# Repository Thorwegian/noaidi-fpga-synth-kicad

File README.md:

# Noaidi FPGA Synth: the board

The KiCad project for the Noaidi synthesizer's circuit board, in
progress. The gateware and firmware that run on it live in
[Thorwegian/noaidi-fpga-synth](https://github.com/Thorwegian/noaidi-fpga-synth),
and the synth itself is presented at [thj.no/synth](https://thj.no/synth/).

## What is on it

The board is a carrier for three off-the-shelf modules and the few parts
around them, numbered as in the picture:

1. **Two DIN MIDI inputs** (J1, J2) through H11L1 optocouplers (U3, U4),
   the six-legged part below each socket: one for the keyboard, one for
   the dev host.
2. **ESP32-S3-DevKitC** (U1) on headers: MIDI, voices, presets and the
   console. The picture shows Espressif's board; the boards in hand are
   copies with the same pin layout (`docs/yd_esp32_s3.md`).
3. **Tang Nano 20K** (U2) on headers: the sound engine.
4. **Adafruit PCM510x I2S DAC module** (U5): analog audio out, on its
   own 3.5 mm jack and on a pin header.
5. **RCA socket** (J3): S/PDIF out.
6. **USB-C socket for power** (J9), into each module's 5 V rail through
   an LM66100 ideal diode (U6, U7).
7. **USB-C socket for data** (J14): the ESP32's USB data pair, below the
   module's USB pins.
8. **Pin headers** for the second SPI bus, two I2C buses, UART0, I2S and
   S/PDIF, the ESP32 module's 5 V beside the UART for a front panel
   board, and 29 test points.
9. **Four RGBW LEDs** (D3–D6) in a chain, on the ESP32's GPIO21 through a
   buffer (U8), for a light inside the case.

Two layers, 78.43 × 160.58 mm by `kicad-cli pcb export stats`, both
filled with ground. The modules, the DIN and RCA sockets, the pin
headers and the test points are through-hole; the other parts are
surface-mount.

The board is made from the circuit in text by script: see The circuit
in text, below.

## Layout

Front copper and silkscreen:

Back copper, mirrored:

The three modules are rendered from 3D models of them, each standing in
a socket of two rows of female pin headers: the Tang Nano 20K from
Sipeed's model (`docs/thirdparty/Tang_Nano_20K_3921.step`), the ESP32
module from the model of the ESP32-S3-DevKitC-1-N8R2
(`docs/thirdparty/ESP32-S3-DEVKITC-1-N8R2.STEP`), the DAC module from
Adafruit's model (`docs/thirdparty/6250 PCM510x I2S DAC.step`). The
first two models have the module's pin headers; Adafruit's has none,
and KiCad's model of a pin header stands in under each of its rows.
Each module's underside is 11.04 mm above the base board: the 8.5 mm of
the socket, from KiCad's model of it, and the 2.54 mm body of the
module's pin headers.

The DIN sockets are rendered from a model made of Lumberg's two
(`docs/thirdparty/lumberg_0105_05_with_pins_of_08-1.step`): the body is
that of Lumberg's model of the 0105 05, with its contacts cut off at
the body's underside, and the solder pins below it are those of poles
1 to 5 and the two ground pins of Lumberg's model of the 8-pole
version, the 0105 08-1. Those pins are where Lumberg's drawing and the
footprint have them, which the 0105 05 model's own are not. The colours
are the project's: dark grey for the plastic, as the part is, and
tinned metal for the contacts and pins.

The RCA socket is rendered from Kycon's model of the part
(`docs/thirdparty/KLPX-0848A-2-x.IGS`), unaltered: the housing is dark,
as that of the black KLPX-0848A-2-B is, and the barrel reaches beyond
the board's bottom edge.

The two USB sockets are rendered from a model of the Hroparts
TYPE-C-31-M-12 that is not its maker's
(`docs/thirdparty/Hroparts_TYPE-C-31-M-12_model_ai03.step`). It is a
simplified one: a single solid in one colour, with twelve solder tails
where the part has sixteen, the two of each supply and ground pair
drawn as one. Its shell, mouth, legs and pegs are where Hroparts'
drawing has them.

The four LEDs are rendered from the model in JLCPCB's library for
OPSCO's SKC6812RGBW-WS, C5378724
(`docs/thirdparty/SKC6812RGBW_model_EasyEDA.step`): 5.1 × 4.9 × 1.6 mm
over its leads, where OPSCO's data sheet has 5.0 × 4.85 × 1.6, with the
cut corner of its top at pad 1.

The ESP32 module's model is from DigiKey's page for the part, the DAC
module's from Adafruit's repository of CAD files on GitHub
([adafruit/Adafruit_CAD_Parts](https://github.com/adafruit/Adafruit_CAD_Parts)).
Of Lumberg's two DIN socket models, the 0105 05's is from DigiKey's
page for the part and the 0105 08-1's from
[Lumberg's page for the 0105](https://www.lumberg.com/en/products/product/0105),
which carries the same file of the 0105 05 as DigiKey. The RCA socket's
model is Kycon's own, and so is its
[dimension drawing](https://cloud.kycon.com/Pub_Eng_Draw/KLPX-0848A-2-x.pdf).
The USB sockets' model is ai03's, from the KiCad library
[ai03-2725/Type-C.pretty](https://github.com/ai03-2725/Type-C.pretty)
on GitHub, which states no licence. The LEDs' model is the one
EasyEDA's library holds for the package
`LED-SMD_4P-4.9-W4.9-LS5.0-BR`, fetched from EasyEDA by
the uuid in `docs/thirdparty/jlcpcb-library/C5378724.json`; it states
no licence either.

## Files

The root folder holds the KiCad project, this README, `AGENTS.md` and
the licence. Scripts go in `scripts/`, documents in `docs/`.

- `AGENTS.md`: the rules for AI agents working in this repository, who
  does what, and where to start reading.
- `noaidi-fpga-synth.kicad_pro`, `.kicad_pcb`, `.kicad_dru`: the KiCad
  project, which holds the board and its design rules. It has no
  schematic: the circuit is in `circuit/`.
- `noaidi-fpga-synth.kicad_sym` and `noaidi-fpga-synth.pretty/`: the
  project's own symbols and footprints (the two modules, the DAC, the
  DIN sockets, the RCA and USB-C connectors). The ESP32 module's
  footprint is Espressif's, from
  [espressif/kicad-libraries](https://github.com/espressif/kicad-libraries)
  (CC-BY-SA 4.0 with the exception KiCad's own libraries have), with a
  keep-out for copper fills under the antenna and, beside each pad of
  pins 23 to 44, a second hole 2.54 mm further out on the same copper:
  Espressif's board has its pin rows 22.86 mm apart, the HW-678 has
  them 25.4 mm apart, and either plugs in. The USB sockets'
  footprint, `USB_C_Receptacle_HRO_TYPE-C-31-M-12`, is the one of that
  name in KiCad's library `Connector_USB` (the same licence), naming a
  3D model that the repository holds: KiCad's names one that KiCad does
  not ship.
- `scripts/render.sh`: makes the board's images on this page, into
  `build/` (the page shows the copies in `docs/images/`), with
  `kicad-cli` (KiCad 10), and with them the view at an angle from the
  other side, the sockets at the board's top edge facing the camera
  (`build/pcb-iso-rear.jpg`); `scripts/crop.py` trims each 3D render to
  the board and the parts on it, what reaches beyond the board's edge
  included, and `scripts/parts_picture.py` numbers the parts in the view
  from above (`build/pcb-parts.jpg`)
- `scripts/render_enclosure.sh`: renders the board in a clear acrylic
  enclosure, lit in the dark by LEDs inside the acrylic, into
  `build/enclosure-<shot>.png`, one picture for each of its shots, with
  `kicad-cli` and Blender; `scripts/enclosure_scene.py` builds the scene
  around the board's 3D model, with an opening in the wall for each part
  at an edge, lists the shots and says how the light is modelled. The
  picture at the top of this page is its shot `left-bottom-low`. The
  enclosure is the picture's and decides nothing about the one that will
  be built.
- `circuit/`: the circuit described in Python with SKiDL, one file
  per sheet (`usb.py`, `esp32.py`, `tang_nano_20k.py`, `test_points.py`),
  the nets that cross sheets in `global_nets.py`, the parts used on more
  than one sheet in `parts.py`, and `board.py` for the whole board. See
  The circuit in text, below. `designators.toml` lists each part's
  designator by the path of tags that leads to the part
  (`esp32.midi1_input.opto` is U3), and `designators.py` gives every part
  its designator from it: the sheets name none. `board.py` writes a new
  part's line into it, with the next free number, and retires the
  designator of a part that is gone. `esp32_minimal.py` is the ESP32-S3-WROOM-1
  module with the least that belongs to it, after Espressif's
  ESP32-S3-DevKitC-1; no sheet uses it, as the board carries the bought
  module.
- `scripts/layout_pictures.py`: pictures of the board's copper and print to judge
  a layout by: the whole board, its quarters, tiles small enough for an
  agent to see every track, each layer with its fill, and the fills
  laid over each other.
- `scripts/fab_files.py`: writes what JLCPCB's order page takes into
  `build/fab/`: the Gerber and drill files as one archive, the list of
  the parts JLCPCB places, and the list of where each of them sits.
- `scripts/cost_estimate.py`: prints what an order of the board costs at
  JLCPCB, delivered to Norway with VAT: the parts and the assembly fees
  fetched from JLCPCB as it runs, the bare boards and shipping at the
  prices read from JLCPCB's quote page.
- `scripts/netlist_import.py`: what KiCad's File > Import > Netlist
  would list for the netlist `circuit/board.py` writes and the board, in
  the dialog's own wording and without running KiCad, so that a mistake
  in the circuit is found before anyone opens the board. It links
  footprints by their tstamps, the dialog's "Link footprints using
  component tstamps (unique ids)", unless it is given `--by-designator`.
  KiCad's dialog is the authority; this is the check that comes first.
- `docs/pins.md`: which pin of which module carries what, the
  connectors, the test points, and each part's name in the code.
  Written by `circuit/board.py`; not edited by hand.
- `docs/requirements.md`: what the board has to do; the circuit and
  the layout are checked against it.
- [`docs/yd_esp32_s3.md`](docs/yd_esp32_s3.md): the YD-ESP32-S3, the
  design of the ESP32-S3 boards in hand, and those boards in detail.
- `docs/thirdparty/`: the vendors' documents the board is drawn from.
  Mechanical: the Tang Nano 20K's dimension drawing (`.pdf`, `.dxf`) and
  3D model (`.step`), the ESP32-S3-DevKitC-1-N8R2's 3D model (`.STEP`),
  the HW-678's manual from its seller (`.pdf`) and the dimension drawing
  of the YD-ESP32-S3, the design it copies, from its designer (`.pdf`),
  the Adafruit PCM510x's 3D model (`.step`) and fab print with its
  dimensions, a 3D model of the Lumberg 0105 05 DIN socket made
  from Lumberg's models of the 0105 05 and the 0105 08-1 (`.step`),
  Kycon's 3D model of the KLPX-0848A-2-x RCA socket (`.IGS`) with its
  dimension drawing, which has the recommended PCB layout, ai03's
  3D model of the Hroparts TYPE-C-31-M-12 USB-C socket (`.step`) and
  EasyEDA's 3D model of the SKC6812 RGBW LED (`.step`).
  Electrical: the Tang Nano 20K's schematic and pinout, the
  GW2AR data sheet, the ESP32-S3-DevKitC-1 user guide and pinouts, and
  Espressif's reference design for that board (v1.1) in a folder of its
  own: the schematic, the layout as a PADS file, the Gerber files, the
  fabrication requirements, the bill of materials and the placement
  list. The YD-ESP32-S3's schematic (V1.4) from its designer. Then the
  Adafruit PCM510x guide and schematic, the 6N138 MIDI input circuit and
  the TOTX1950A optical transmitter's data sheet. The board's own parts,
  from the links in their symbols' Datasheet fields: the LM66100 ideal
  diode (U6, U7), the H11L1 optocoupler (U3, U4; onsemi's data sheet,
  which the symbol names, and Everlight's, whose part is the one
  chosen), the 1N4148W diode (D1, D2), the Lumberg 0105 DIN socket
  (J1, J2), the Kycon KLPX RCA socket (J3), the Hroparts
  TYPE-C-31-M-12 USB-C socket (J9, J14; drawing) and OPSCO's SKC6812RGBW
  LED (D3–D6). Two parts that are
  not on the board: the 6N138 optocoupler and the GCT USB4085 USB-C
  receptacle (specification and drawing). The parts of
  `circuit/esp32_minimal.py`, which are not on the board either: the
  ESP32-S3-WROOM-1 module and JSCJ's SS8050 transistor.

## Build tools

`kicad-cli` (KiCad 10), `pdftoppm` (poppler-utils), `blender` (4, with
Cycles, for `scripts/render_enclosure.sh`) and
`java` (25, for Freerouting, whose jar `scripts/route.sh` fetches into
`build/tools/`) come from the system's packages, and so does the Python
with KiCad's `pcbnew` module and Pillow (python3-pil) that the scripts
which read the board file run under. The other Python
tools are listed in
`scripts/requirements.txt` and live in a virtual environment, `.venv/`
at the root, which is not committed:

    python3 -m venv .venv
    .venv/bin/pip install -r scripts/requirements.txt
    source .venv/bin/activate

- `skidl`: circuits described in Python. It is not in Ubuntu's packages.
  It finds KiCad's symbol libraries through the environment variable
  `KICAD10_SYMBOL_DIR` (`/usr/share/kicad/symbols` on Ubuntu). It also
  looks for KiCad 5 to 9 on every run, and warns about each one that is
  not installed. `circuit/.skidlcfg` gives those five an empty answer; it
  is read from SKiDL's own folder, where it is put once on each machine
  (`~/Library/Application Support/skidl` on macOS):

      mkdir -p ~/.local/share/skidl
      cp circuit/.skidlcfg ~/.local/share/skidl/
- `pillow`: for `scripts/crop.py` and `scripts/parts_picture.py`.

## The circuit in text

`circuit/` describes the board's circuit in Python, and it is where the
circuit is designed. It holds the parts chosen for fabrication: 0805
resistors and capacitors, H11L1 optocouplers, two surface-mount USB-C
sockets (one for power, one for the ESP32's USB data), no ferrite
bead, and one S/PDIF coaxial output (J3, the 96 kHz stream; the 48 kHz
stream is on its header only).

Copyright © 2026 Thor H. Linløkken <thj@thj.no>
License: [CERN-OHL-S v2](LICENSE.txt)

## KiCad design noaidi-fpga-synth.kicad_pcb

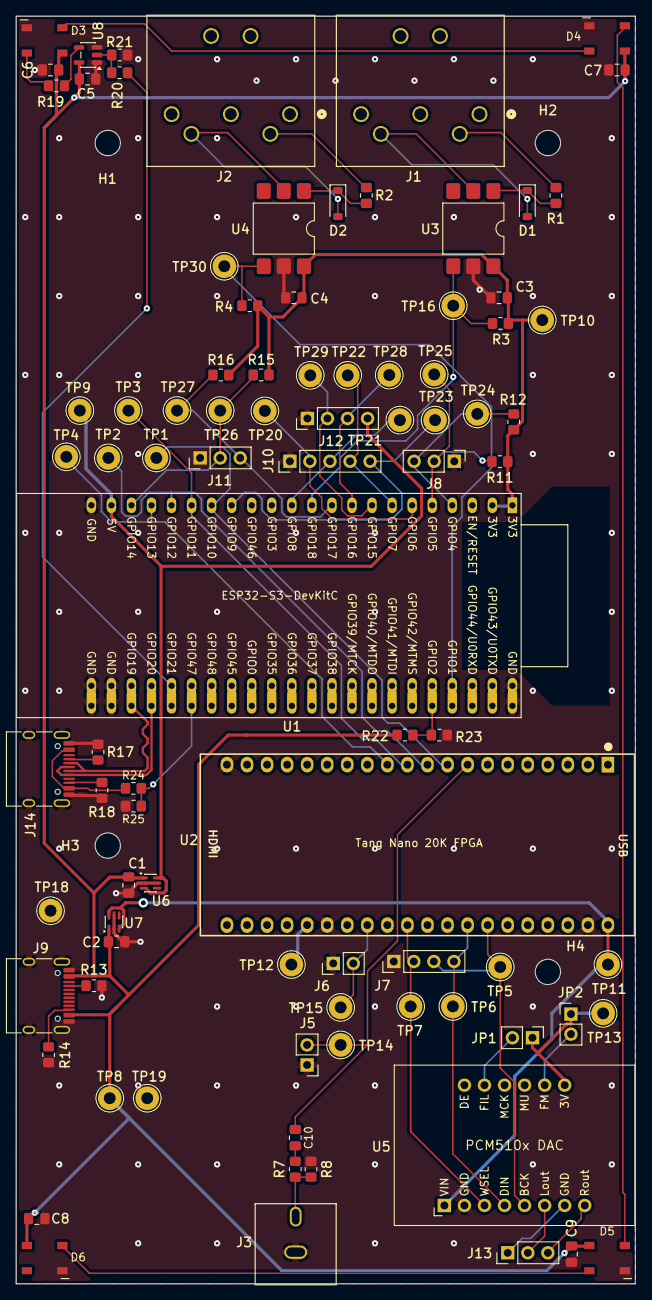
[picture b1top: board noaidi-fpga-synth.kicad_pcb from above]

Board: 2 copper layers, 78.4 x 160.6 mm, 93 parts (0 on the bottom side), 57 nets.

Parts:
C1, C2: 1u; C_0805_2012Metric_Pad1.18x1.45mm_HandSolder
C3, C4, C6, C7, C8, C9, C10: 100n; C_0805_2012Metric_Pad1.18x1.45mm_HandSolder
C5: 10u; C_0805_2012Metric_Pad1.18x1.45mm_HandSolder
D1, D2: 1N4148W; D_SOD-123
D3, D4, D5, D6: LED_SKC6812RGBW; LED_SKC6812RGBW_5.0x4.85mm
H1, H2, H3, H4: MountingHole; MountingHole_3.2mm_M3
J1, J2: Lumberg_0105_05
J3: Conn_Coaxial; RCA_Kycon_KLPX-0848A
J5, J6: Conn_01x02_Pin; PinHeader_1x02_P2.54mm_Vertical
J7, J12: Conn_01x04_Pin; PinHeader_1x04_P2.54mm_Vertical
J8, J11, J13: Conn_01x03_Pin; PinHeader_1x03_P2.54mm_Vertical
J9, J14: USB_C_Receptacle_USB2.0_16P; USB_C_Receptacle_HRO_TYPE-C-31-M-12
J10: Conn_01x05_Pin; PinHeader_1x05_P2.54mm_Vertical
JP1, JP2: Jumper_2_Open; PinHeader_1x02_P2.54mm_Vertical
R1, R2, R7: 220; R_0805_2012Metric_Pad1.20x1.40mm_HandSolder
R3, R4, R19: 470; R_0805_2012Metric_Pad1.20x1.40mm_HandSolder
R8: 120; R_0805_2012Metric_Pad1.20x1.40mm_HandSolder
R11, R12, R15, R16, R23: 4.7k; R_0805_2012Metric_Pad1.20x1.40mm_HandSolder
R13, R14, R17, R18: 5.1k; R_0805_2012Metric_Pad1.20x1.40mm_HandSolder
R20: 1k; R_0805_2012Metric_Pad1.20x1.40mm_HandSolder
R21, R22: 10k; R_0805_2012Metric_Pad1.20x1.40mm_HandSolder
R24: 100k; R_0805_2012Metric_Pad1.20x1.40mm_HandSolder
R25: 150k; R_0805_2012Metric_Pad1.20x1.40mm_HandSolder
TP1, TP2, TP3, TP4, TP5, TP6, TP7, TP8, TP9, TP10, TP11, TP12, TP13, TP14, TP15, TP16, TP18, TP19, TP20, TP21, TP22, TP23, TP24, TP25, TP26, TP27, TP28, TP29, TP30: TestPoint; TestPoint_THTPad_D3.0mm_Drill1.5mm
U1: ESP32-S3-DevKitC
U2: Tang_Nano_20K; DIP-40_TangNano20K
U3, U4: H11L1; SMDIP-6_W9.53mm
U5: Adafruit_PCM510x
U6, U7: LM66100DCK; SOT-363_SC-70-6
U8: 74AHCT1G125; SOT-23-5

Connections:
DAC_FIL: JP1.2, U5.13
DAC_FM: JP2.2, U5.10
DAC_OUT_G: J13.1, U5.7
DAC_OUT_L: J13.2, U5.6
DAC_OUT_R: J13.3, U5.8
ESP_3V3: C3.1, C4.1, R3.1, R4.1, R11.1, R12.1, R15.1, R16.1, TP10.1, U1.1, U1.2, U3.6, U4.6
ESP_5V: J12.4, TP9.1, U1.21, U6.3, U6.6
EXT_5V: C1.1, C2.1, C5.1, C6.1, C7.1, C8.1, C9.1, D3.3, D4.3, D5.3, D6.3, J9.A4, J9.A9, J9.B4, J9.B9, R22.1, TP8.1, U6.1, U7.1, U8.5
EXT_5V_SENSE: R22.2, R23.1, U1.40
GND: C1.2, C2.2, C3.2, C4.2, C5.2, C6.2, C7.2, C8.2, C9.2, D3.1, D4.1, D5.1, D6.1, J3.2, J5.1, J6.1, J7.1, J8.1, J9.A1, J9.A12, J9.B1, J9.B12, J9.SH, J10.1, J11.1, J12.1, J14.A1, J14.A12, J14.B1, J14.B12, J14.SH, R8.2, R13.2, R14.2, R17.2, R18.2, R21.2, R23.2, R25.2, TP18.1, TP19.1, U1.22, U1.23, U1.24, U1.44, U2.20, U2.26, U2.39, U3.5, U4.5, U5.2, U6.2, U6.5, U7.2, U7.5, U8.1, U8.3
I2C0_SCL: J8.2, R11.2, TP25.1, U1.5
I2C0_SDA: J8.3, R12.2, TP24.1, U1.4
I2C1_SCL: J11.2, R15.2, TP26.1, U1.20
I2C1_SDA: J11.3, R16.2, TP27.1, U1.10
I2S_BCK: J7.3, TP5.1, U2.34, U5.5
I2S_DATA: J7.4, TP6.1, U2.33, U5.4
I2S_WS: J7.2, TP7.1, U2.30, U5.3
LED_1_DOUT: D3.4, D4.2
LED_2_DOUT: D4.4, D5.2
LED_3_DOUT: D5.4, D6.2
LED_BUFFER_IN: R20.2, R21.1, U8.2
LED_DATA: R20.1, U1.27
LED_DATA_5V: R19.1, U8.4
LED_DIN: D3.2, R19.2
MIDI1_LED_A: D1.1, R1.2, U3.1
MIDI1_LED_K: D1.2, J1.5, U3.2
MIDI1_RX: R3.2, TP16.1, U1.11, U3.4
MIDI1_SOURCE: J1.4, R1.1
MIDI2_LED_A: D2.1, R2.2, U4.1
MIDI2_LED_K: D2.2, J2.5, U4.2
MIDI2_RX: R4.2, TP30.1, U1.41, U4.4
MIDI2_SOURCE: J2.4, R2.1
NANO_3V3: TP12.1, U2.25
NANO_5V: TP11.1, U2.40, U5.1, U7.3, U7.6
PANEL_UART_RX: J12.3, TP28.1, U1.9
PANEL_UART_TX: J12.2, TP29.1, U1.8
PCM_3V3: JP1.1, JP2.1, TP13.1, U5.9
SPDIF0: C10.1, J5.2, TP14.1, U2.8
SPDIF0_AC: C10.2, R7.1
SPDIF0_COAX: J3.1, R7.2, R8.1
SPDIF1: J6.2, TP15.1, U2.28
SPI2_CS_N: TP1.1, U1.16, U2.9
SPI2_MISO: TP4.1, U1.19, U2.12
SPI2_MOSI: TP3.1, U1.17, U2.11
SPI2_SCLK: TP2.1, U1.18, U2.10
SPI3_CS_N: J10.2, TP20.1, U1.6
SPI3_MISO: J10.5, TP23.1, U1.15
SPI3_MOSI: J10.4, TP22.1, U1.7
SPI3_SCLK: J10.3, TP21.1, U1.12
USB_D+: J14.A6, J14.B6, U1.26
USB_D-: J14.A7, J14.B7, U1.25
USB_DATA_CC1: J14.A5, R17.1
USB_DATA_CC2: J14.B5, R18.1
USB_DATA_VBUS: J14.A4, J14.A9, J14.B4, J14.B9, R24.1
USB_DATA_VBUS_SENSE: R24.2, R25.1, U1.28
USB_POWER_CC1: J9.A5, R13.1
USB_POWER_CC2: J9.B5, R14.1

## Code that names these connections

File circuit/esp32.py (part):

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    USB_D_MINUS += esp["GPIO19"]
    USB_D_PLUS += esp["GPIO20"]

    SPI2_CS_N += esp["GPIO10"]
    SPI2_MOSI += esp["GPIO11"]
    SPI2_SCLK += esp["GPIO12"]
    SPI2_MISO += esp["GPIO13"]
    for line in (SPI2_CS_N, SPI2_SCLK, SPI2_MOSI, SPI2_MISO):
        test_point(line)

    spi3_header = pin_header(5, tag="spi3_header")
    GND += spi3_header[1]
    SPI3_CS_N += esp["GPIO6"], spi3_header[2]
    SPI3_SCLK += esp["GPIO8"], spi3_header[3]
    SPI3_MOSI += esp["GPIO7"], spi3_header[4]
    SPI3_MISO += esp["GPIO9"], spi3_header[5]
    for line in (SPI3_CS_N, SPI3_SCLK, SPI3_MOSI, SPI3_MISO):
        test_point(line)

    I2C0_SCL += esp["GPIO5"]
    I2C0_SDA += esp["GPIO4"]
    I2C1_SCL += esp["GPIO14"]
    I2C1_SDA += esp["GPIO17"]
    i2c_port(I2C0_SCL, I2C0_SDA, ESP_3V3, GND, tag="i2c0_port")
    i2c_port(I2C1_SCL, I2C1_SDA, ESP_3V3, GND, tag="i2c1_port")

    panel_uart_header = pin_header(4, tag="panel_uart_header")
    GND += panel_uart_header[1]
    PANEL_UART_TX += esp["GPIO15"], panel_uart_header[2]
    PANEL_UART_RX += esp["GPIO16"], panel_uart_header[3]
    # The panel board's supply, on the pin after the UART so that a three-pin
    # cable still fits the first three.
    ESP_5V += panel_uart_header[4]
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    test_point(PANEL_UART_TX)

    led_data = Net("LED_DATA")
    led_data += esp["GPIO21"]
    led_chain(led_data, EXT_5V, GND, pixels=4, tag="led_chain")

    # Whether the power socket is in, read as a voltage rather than as a logic
    # level, so the firmware can tell a charger from a computer's port: 1.52 V
    # at 4.75 V, 1.60 V at 5.0 V and 1.68 V at 5.25 V, at 340 uA.
    ext_5v_sense = Net("EXT_5V_SENSE")
    ext_5v_sense += esp["GPIO2"]
    supply_sense(EXT_5V, ext_5v_sense, GND, top_value="10k", bottom_value="4.7k",
                 tag="ext_5v_sense")

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    # is unpowered whenever the computer is plugged in and the charger is not,
    # and the 100 k then lets at most 55 uA into the dead pin.
    usb_data_vbus_sense = Net("USB_DATA_VBUS_SENSE")
    usb_data_vbus_sense += esp["GPIO47"]
    supply_sense(USB_DATA_VBUS, usb_data_vbus_sense, GND, top_value="100k", bottom_value="150k",
                 tag="usb_data_vbus_sense")

    MIDI1_RX += esp["GPIO18"]
    MIDI2_RX += esp["GPIO1"]
    midi_input("MIDI1", MIDI1_RX, ESP_3V3, GND, tag="midi1_input")
    midi_input("MIDI2", MIDI2_RX, ESP_3V3, GND, tag="midi2_input")

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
